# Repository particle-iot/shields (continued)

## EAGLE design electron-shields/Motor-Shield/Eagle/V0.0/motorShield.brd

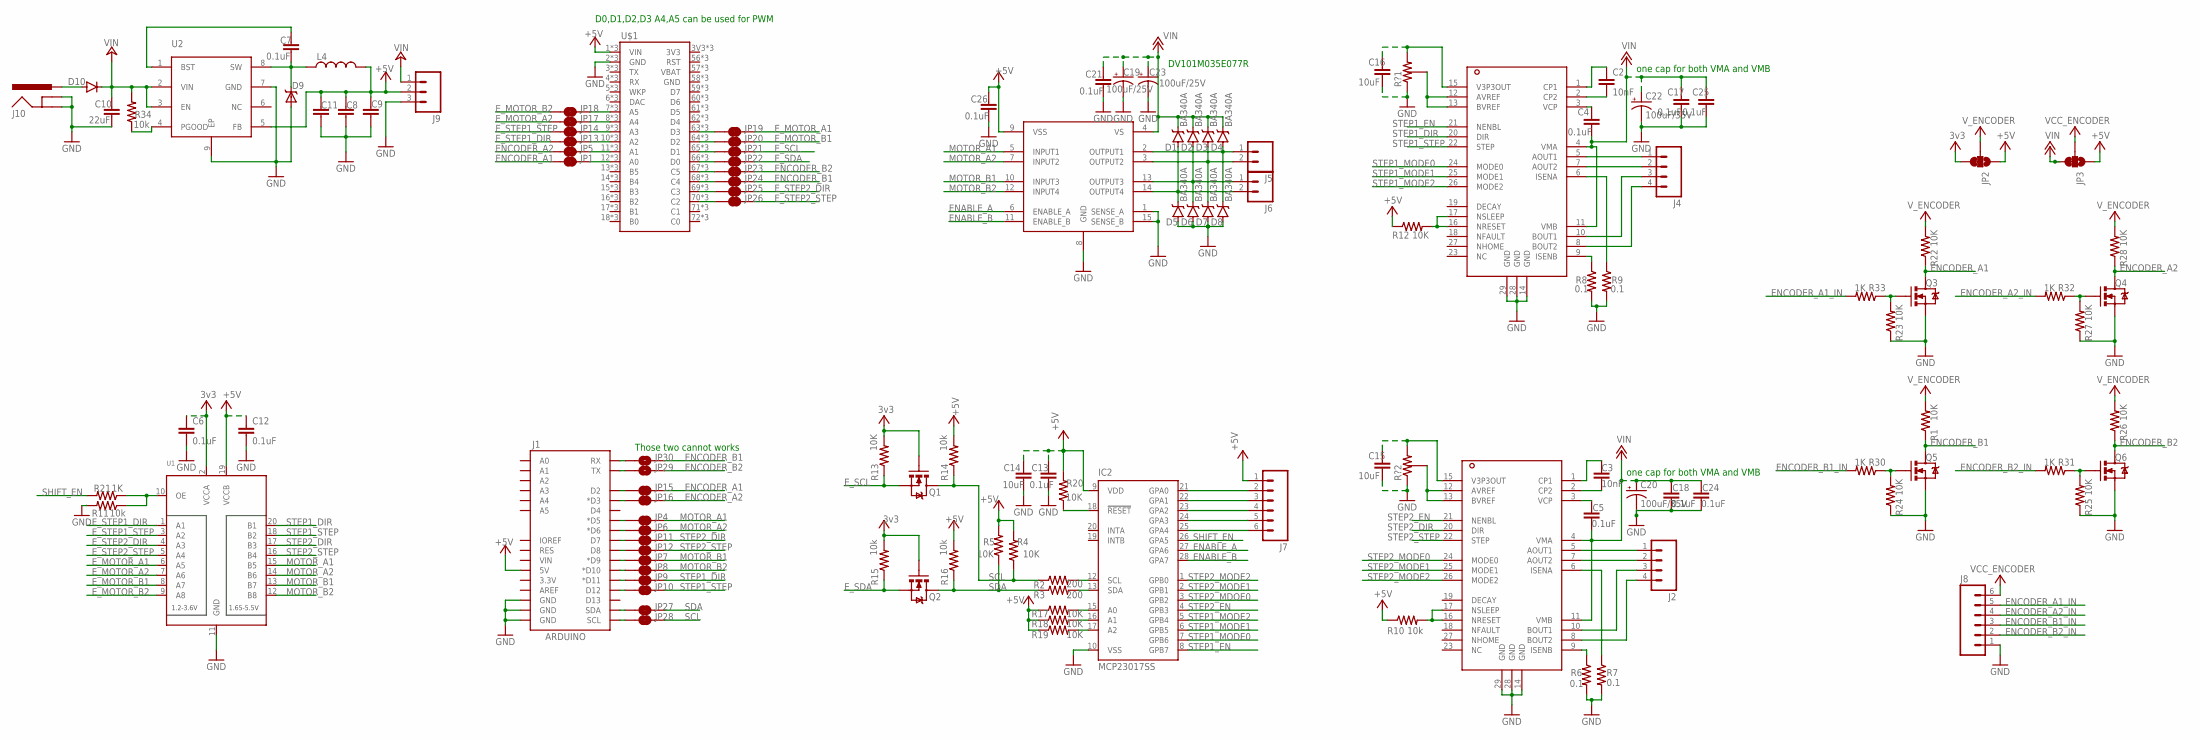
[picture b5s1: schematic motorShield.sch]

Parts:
C2, C3: 10nF; 0603
C4, C5, C6, C12, C13, C17, C18, C21, C24, C25, C26: 0.1uF; 0603
C7: 0.1uF; 0603-CAP
C8, C9, C11: 10UF10V10%(0805); 0805-CAP
C10: 22uF; 1210
C14, C15, C16: 10uF; 0603
C19, C23: 100uF/25V; PANASONIC_D
C20, C22: 100uF/35V; PANASONIC_D
D1, D2, D3, D4, D5, D6, D7, D8: BA340A; SMA-DIODE
D9: DIODE_SCHOTTKYA; DIODE_SMA
D10: DIODEB; DIODE-DO-220AA_NT(SMP)
IC2: MCP23017SS; SSOP28
J1: ARDUINO; UNO_R3_SHIELD_LOCK
J2, J4: M04SCREW; SCREWTERMINAL-3.5MM-4
J5, J6: M023.5MM_LOCK; SCREWTERMINAL-3.5MM-2_LOCK
J7, J8: M06POLAR; MOLEX-1X6
J9: M03SCREW; SCREWTERMINAL-3.5MM-3
J10: POWER_JACKPTH; POWER_JACK_PTH
JP1, JP4, JP5, JP6, JP7, JP8, JP9, JP10, JP11, JP12, JP13, JP14, JP15, JP16, JP17, JP18, JP19, JP20, JP21, JP22, JP23, JP24, JP25, JP26, JP27, JP28: JUMPER-PAD-2-NC_BY_TRACENO_SILK; PAD-JUMPER-2-NC_BY_TRACE_NO_SILK
JP2, JP3: JUMPER-PAD-3-2OF3_NC_BY_TRACE_LARGE; PAD-JUMPER-3-2OF3_NC_BY_TRACE_YES_SILK_LARGE
JP29, JP30: JUMPER-PAD-2-NO; PAD-JUMPER-2-NO_NO_SILK
L4: INDUCTOR4818; I4818
Q1, Q2, Q3, Q4, Q5, Q6: MOSFET-NCHANNELBSS138; SOT23
R1, R4, R5, R12, R13, R17, R18, R19, R20, R22, R23, R24, R25, R26, R27, R28: 10K; R0603
R2, R3: 200; R0603
R6, R7, R8, R9: 0.1; M1206
R10, R14, R15, R16: 10k; R0603
R11, R34: 10k; 0603-RES
R21: 1K; 0603-RES
R30, R31, R32, R33: 1K; R0603
R?1, R?2: POTENTIAL_RESISTOR
U1: TXB0108PWR; TSSOP20
U2: ADP2303; ADP2302
U$1: ELECTRONDUALROW; ELECTRON_DUAL-ROW
U?1, U?3: DRV8825
U?2: L298

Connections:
3V3: U$1.3V3, U$1.55 (3V3), U$1.91 (3V3)
+3V3: C6.1 (ANODE), JP2.3, Q1.1 (G), Q2.1 (G), R13.2, R15.2, U1.2 (VCCA)
+5V: C8.2, C9.2, C11.1, C12.1 (ANODE), C13.1 (ANODE), C14.1 (ANODE), C26.1 (ANODE), IC2.9 (VDD), J1.5V, J7.1, J8.6, J9.2, JP2.1, JP2.2, JP3.1, JP3.2, L4.2, R1.2, R4.2, R5.2, R10.1, R12.1, R14.2, R16.2, R17.1, R18.1, R19.1, R20.2, R22.2, R26.2, R28.2, U1.19 (VCCB), U2.5 (FB), U$1.1 (VIN), U$1.37 (VIN), U$1.VIN, U?2.9 (VSS)
+12V: C4.2 (CATHODE), C5.2 (CATHODE), C17.1 (ANODE), C18.1 (ANODE), C19.+, C20.+, C21.1 (ANODE), C22.+, C23.+, C24.1 (ANODE), C25.1 (ANODE), D1.C, D2.C, D3.C, D4.C, JP3.3, U?1.4 (VMA), U?1.11 (VMB), U?2.4 (VS), U?3.4 (VMA), U?3.11 (VMB)
+24V: C10.1, D10.CATHODE, J9.1, R34.2, U2.2 (VIN), U2.3 (EN)
ENABLE_A: IC2.27 (GPA6), U?2.6 (ENABLE_A)
ENABLE_B: IC2.28 (GPA7), U?2.11 (ENABLE_B)
ENCODER_A1: JP1.1, JP15.2, Q3.3 (D), R22.1
ENCODER_A1_IN: J8.5, R33.2
ENCODER_A2: JP5.1, JP16.2, Q4.3 (D), R28.1
ENCODER_A2_IN: J8.4, R32.2
ENCODER_B1: JP24.2, JP30.2, Q5.3 (D), R1.1
ENCODER_B1_IN: J8.3, R30.2
ENCODER_B2: JP23.2, JP29.2, Q6.3 (D), R26.1
ENCODER_B2_IN: J8.2, R31.2
E_MOTOR_A1: JP19.2, U1.6 (A5)
E_MOTOR_A2: JP17.1, U1.7 (A6)
E_MOTOR_B1: JP20.2, U1.8 (A7)
E_MOTOR_B2: JP18.1, U1.9 (A8)
E_SCL: JP21.2, Q1.2 (S), R13.1
E_SDA: JP22.2, Q2.2 (S), R15.1
E_STEP1_DIR: JP13.1, U1.1 (A1)
E_STEP1_STEP: JP14.1, U1.3 (A2)
E_STEP2_DIR: JP25.2, U1.4 (A3)
E_STEP2_STEP: JP26.2, U1.5 (A4)
GND: C6.2 (CATHODE), C8.1, C9.1, C10.2, C11.2, C12.2 (CATHODE), C13.2 (CATHODE), C14.2 (CATHODE), C15.2 (CATHODE), C16.2 (CATHODE), C17.2 (CATHODE), C18.2 (CATHODE), C19.-, C20.-, C21.2 (CATHODE), C22.-, C23.-, C24.2 (CATHODE), C25.2 (CATHODE), C26.2 (CATHODE), D5.A, D6.A, D7.A, D8.A, D9.ANODE, IC2.10 (VSS), J1.GND@0 (GND), J1.GND@1 (GND), J1.GND@2 (GND), J8.1, J9.3, J10.GND, J10.GNDBREAK, Q3.2 (S), Q4.2 (S), Q5.2 (S), Q6.2 (S), R6.2, R7.2, R8.2, R9.2, R11.2, R23.1, R24.1, R25.1, R27.1, R?1.1, R?2.1, U1.11 (GND), U2.7 (GND), U2.9 (EP), U$1.2 (GND), U$1.38 (GND), U$1.58 (GND), U$1.94 (GND), U$1.GND, U$1.GND@2 (GND), U?1.14 (GND), U?1.28 (GND), U?1.29 (GND), U?2.1 (SENSE_A), U?2.8 (GND), U?2.15 (SENSE_B), U?3.14 (GND), U?3.28 (GND), U?3.29 (GND)
MOTOR_A1: JP4.2, U1.15 (B5), U?2.5 (INPUT1)
MOTOR_A2: JP6.2, U1.14 (B6), U?2.7 (INPUT2)
MOTOR_B1: JP7.2, U1.13 (B7), U?2.10 (INPUT3)
MOTOR_B2: JP8.2, U1.12 (B8), U?2.12 (INPUT4)
unnamed: IC2.13 (SDA), R3.2
unnamed: IC2.12 (SCL), R2.2
unnamed: C3.2 (CATHODE), U?3.2 (CP2)
unnamed: C3.1 (ANODE), U?3.1 (CP1)
unnamed: C2.2 (CATHODE), U?1.2 (CP2)
unnamed: C2.1 (ANODE), U?1.1 (CP1)
unnamed: R6.1, U?3.9 (ISENB)
unnamed: R7.1, U?3.6 (ISENA)
unnamed: R10.2, U?3.16 (NRESET), U?3.17 (NSLEEP)
unnamed: D4.A, D8.C, J5.1, U?2.2 (OUTPUT1)
unnamed: J2.1, U?3.5 (AOUT1)
unnamed: J2.2, U?3.7 (AOUT2)
unnamed: J2.3, U?3.10 (BOUT1)
unnamed: J2.4, U?3.8 (BOUT2)
unnamed: R8.1, U?1.9 (ISENB)
unnamed: R9.1, U?1.6 (ISENA)
unnamed: J4.1, U?1.5 (AOUT1)
unnamed: J4.2, U?1.7 (AOUT2)
unnamed: J4.3, U?1.10 (BOUT1)
unnamed: J4.4, U?1.8 (BOUT2)
unnamed: C4.1 (ANODE), U?1.3 (VCP)
unnamed: C5.1 (ANODE), U?3.3 (VCP)
unnamed: D3.A, D7.C, J5.2, U?2.3 (OUTPUT2)
unnamed: D2.A, D6.C, J6.1, U?2.13 (OUTPUT3)
unnamed: D1.A, D5.C, J6.2, U?2.14 (OUTPUT4)
unnamed: R11.1, R21.1, U1.10 (OE)
unnamed: IC2.15 (A0), R17.2
unnamed: R12.2, U?1.16 (NRESET), U?1.17 (NSLEEP)
unnamed: IC2.16 (A1), R18.2
unnamed: IC2.17 (A2), R19.2
unnamed: R?1.3, U?1.12 (AVREF), U?1.13 (BVREF)
unnamed: IC2.18 (!RESET), R20.1
unnamed: J1.SCL, JP28.1
unnamed: R?2.3, U?3.12 (AVREF), U?3.13 (BVREF)
unnamed: J1.SDA, JP27.1
unnamed: J1.D5 (*D5), JP4.1
unnamed: J1.D6 (*D6), JP6.1
unnamed: J1.D9 (*D9), JP7.1
unnamed: J1.D10 (*D10), JP8.1
unnamed: J1.D11 (*D11), JP9.1
unnamed: J1.D12, JP10.1
unnamed: J1.D8, JP12.1
unnamed: J1.D7, JP11.1
unnamed: IC2.25 (GPA4), J7.6
unnamed: IC2.24 (GPA3), J7.5
unnamed: J1.D2, JP15.1
unnamed: J1.D3 (*D3), JP16.1
unnamed: IC2.23 (GPA2), J7.4
unnamed: IC2.22 (GPA1), J7.3
unnamed: IC2.21 (GPA0), J7.2
unnamed: Q4.1 (G), R27.2, R32.1
unnamed: Q5.1 (G), R24.2, R30.1
unnamed: Q6.1 (G), R25.2, R31.1
unnamed: C7.2, D9.CATHODE, L4.1, U2.8 (SW)
unnamed: Q3.1 (G), R23.2, R33.1
unnamed: C7.1, U2.1 (BST)
unnamed: R34.1, U2.4 (PGOOD)
unnamed: D10.ANODE, J10.PWR
unnamed: JP1.2, U$1.12 (A0), U$1.48 (A0), U$1.A0
unnamed: JP5.2, U$1.11 (A1), U$1.47 (A1), U$1.A1
unnamed: JP13.2, U$1.10 (A2), U$1.46 (A2), U$1.A2
unnamed: JP14.2, U$1.9 (A3), U$1.45 (A3), U$1.A3
unnamed: JP17.2, U$1.8 (A4), U$1.44 (A4), U$1.A4
unnamed: JP18.2, U$1.7 (A5), U$1.43 (A5), U$1.A5
unnamed: JP19.1, U$1.63 (D3), U$1.99 (D3), U$1.D3
unnamed: JP20.1, U$1.64 (D2), U$1.100 (D2), U$1.D2
unnamed: JP21.1, U$1.65 (D1), U$1.101 (D1), U$1.D1
unnamed: JP22.1, U$1.66 (D0), U$1.102 (D0), U$1.D0
unnamed: JP23.1, U$1.67 (C5), U$1.103 (C5), U$1.C5
unnamed: JP24.1, U$1.68 (C4), U$1.104 (C4), U$1.C4
unnamed: JP25.1, U$1.69 (C3), U$1.105 (C3), U$1.C3
unnamed: JP26.1, U$1.70 (C2), U$1.106 (C2), U$1.C2
unnamed: C15.1 (ANODE), R?2.2, U?3.15 (V3P3OUT)
unnamed: J1.TX, JP29.1
unnamed: J1.RX, JP30.1
unnamed: C16.1 (ANODE), R?1.2, U?1.15 (V3P3OUT)
SCL: JP28.2, Q1.3 (D), R2.1, R4.1, R14.1
SDA: JP27.2, Q2.3 (D), R3.1, R5.1, R16.1
SHIFT_EN: IC2.26 (GPA5), R21.2
STEP1_DIR: JP9.2, U1.20 (B1), U?1.20 (DIR)
STEP1_EN: IC2.8 (GPB7), U?1.21 (NENBL)
STEP1_MODE0: IC2.7 (GPB6), U?1.24 (MODE0)
STEP1_MODE1: IC2.6 (GPB5), U?1.25 (MODE1)
STEP1_MODE2: IC2.5 (GPB4), U?1.26 (MODE2)
STEP1_STEP: JP10.2, U1.18 (B2), U?1.22 (STEP)
STEP2_DIR: JP11.2, U1.17 (B3), U?3.20 (DIR)
STEP2_EN: IC2.4 (GPB3), U?3.21 (NENBL)
STEP2_MDOE0: IC2.3 (GPB2)
STEP2_MODE0: U?3.24 (MODE0)
STEP2_MODE1: IC2.2 (GPB1), U?3.25 (MODE1)
STEP2_MODE2: IC2.1 (GPB0), U?3.26 (MODE2)
STEP2_STEP: JP12.2, U1.16 (B4), U?3.22 (STEP)

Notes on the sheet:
D0,D1,D2,D3 A4,A5 can be used for PWM
DV101M035E077R
Those two cannot works
one cap for both VMA and VMB

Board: 2 copper layers, 123 parts (0 on the bottom side), 120 nets, no tracks yet.

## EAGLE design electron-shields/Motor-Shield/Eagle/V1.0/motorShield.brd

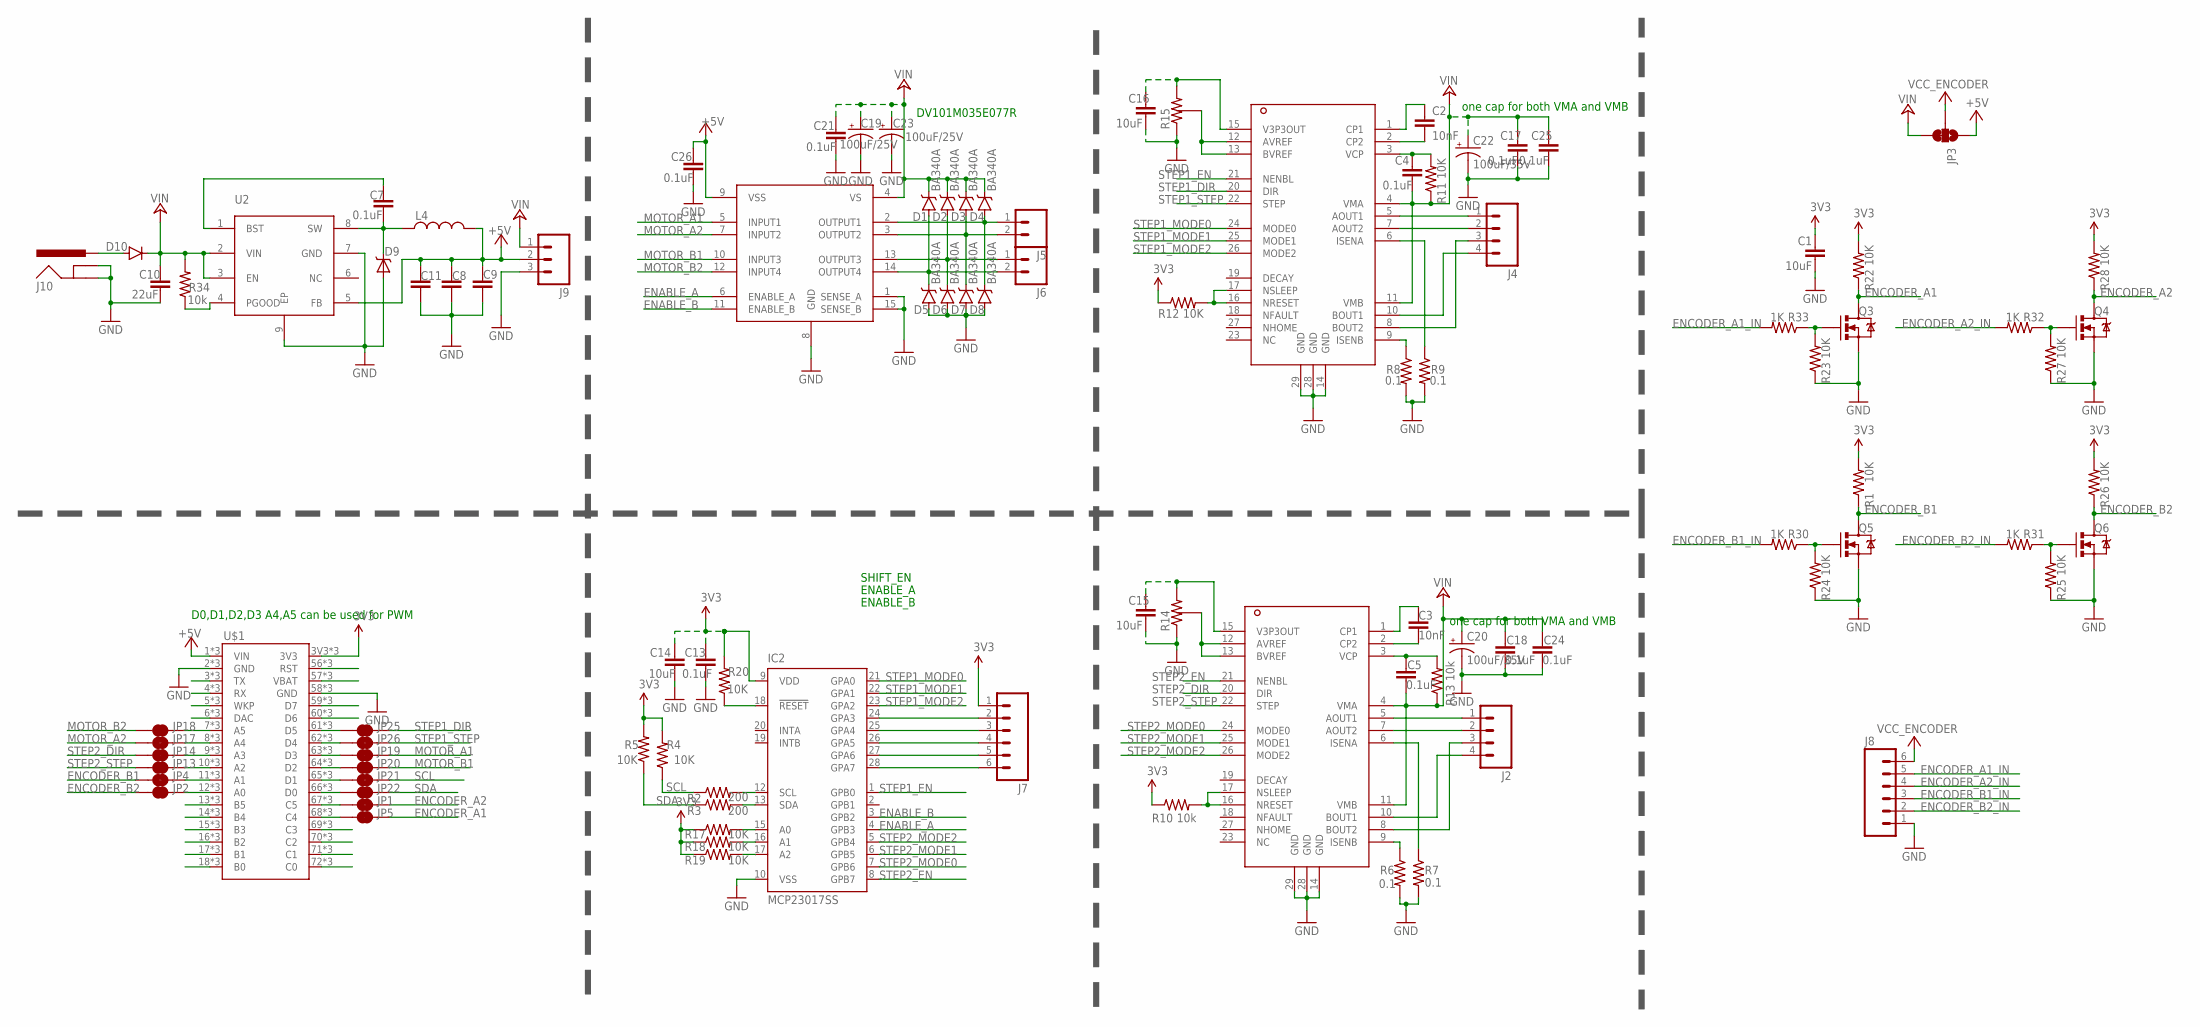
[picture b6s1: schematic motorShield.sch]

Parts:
C1, C14, C15, C16: 10uF; 0603
C2, C3: 10nF; 0603
C4, C5, C13, C17, C18, C21, C24, C25, C26: 0.1uF; 0603
C7: 0.1uF; 0603-CAP
C8, C9, C11: 10UF10V10%(0805); 0805-CAP
C10: 22uF; 1210
C19, C23: 100uF/25V; PANASONIC_D
C20, C22: 100uF/35V; PANASONIC_D
D1, D2, D3, D4, D5, D6, D7, D8: BA340A; SMA-DIODE
D9: DIODE_SCHOTTKYA; DIODE_SMA
D10: DIODEB; DIODE-DO-220AA_NT(SMP)
IC2: MCP23017SS; SSOP28
J2, J4: M04SCREW; SCREWTERMINAL-3.5MM-4
J5, J6: M023.5MM_LOCK; SCREWTERMINAL-3.5MM-2_LOCK
J7, J8: M06POLAR; MOLEX-1X6
J9: M03SCREW; SCREWTERMINAL-3.5MM-3
J10: POWER_JACKPTH; POWER_JACK_PTH
JP1, JP2, JP4, JP5, JP13, JP14, JP17, JP18, JP19, JP20, JP21, JP22, JP25, JP26: JUMPER-PAD-2-NC_BY_TRACENO_SILK; PAD-JUMPER-2-NC_BY_TRACE_NO_SILK
JP3: JUMPER-PAD-3-2OF3_NC_BY_TRACE_LARGE; PAD-JUMPER-3-2OF3_NC_BY_TRACE_YES_SILK_LARGE
L4: INDUCTOR4818; I4818
Q3, Q4, Q5, Q6: MOSFET-NCHANNELBSS138; SOT23
R1, R4, R5, R11, R12, R17, R18, R19, R20, R22, R23, R24, R25, R26, R27, R28: 10K; R0603
R2, R3: 200; R0603
R6, R7, R8, R9: 0.1; M1206
R10, R13: 10k; R0603
R14, R15: POTENTIAL_RESISTOR; POTENTIAL_RESISTOR_2
R30, R31, R32, R33: 1K; R0603
R34: 10k; 0603-RES
U2: ADP2303; ADP2302
U$1: ELECTRONDUALROW; ELECTRON_DUAL-ROW
U?1, U?3: DRV8825
U?2: L298

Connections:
+5V: C8.2, C9.2, C11.1, C26.1 (ANODE), J8.6, J9.2, JP3.1, JP3.2, L4.2, U2.5 (FB), U$1.1 (VIN), U$1.37 (VIN), U$1.VIN, U?2.9 (VSS)
+24V: C4.2 (CATHODE), C5.2 (CATHODE), C10.1, C17.1 (ANODE), C18.1 (ANODE), C19.+, C20.+, C21.1 (ANODE), C22.+, C23.+, C24.1 (ANODE), C25.1 (ANODE), D1.C, D2.C, D3.C, D4.C, D10.CATHODE, J9.1, JP3.3, R11.1, R13.1, R34.2, U2.2 (VIN), U2.3 (EN), U?1.4 (VMA), U?1.11 (VMB), U?2.4 (VS), U?3.4 (VMA), U?3.11 (VMB)
ENABLE_A: IC2.4 (GPB3), U?2.6 (ENABLE_A)
ENABLE_B: IC2.3 (GPB2), U?2.11 (ENABLE_B)
ENCODER_A1: JP5.2, Q3.3 (D), R22.1
ENCODER_A1_IN: J8.5, R33.2
ENCODER_A2: JP1.2, Q4.3 (D), R28.1
ENCODER_A2_IN: J8.4, R32.2
ENCODER_B1: JP4.1, Q5.3 (D), R1.1
ENCODER_B1_IN: J8.3, R30.2
ENCODER_B2: JP2.1, Q6.3 (D), R26.1
ENCODER_B2_IN: J8.2, R31.2
GND: C1.2 (CATHODE), C8.1, C9.1, C10.2, C11.2, C13.2 (CATHODE), C14.2 (CATHODE), C15.2 (CATHODE), C16.2 (CATHODE), C17.2 (CATHODE), C18.2 (CATHODE), C19.-, C20.-, C21.2 (CATHODE), C22.-, C23.-, C24.2 (CATHODE), C25.2 (CATHODE), C26.2 (CATHODE), D5.A, D6.A, D7.A, D8.A, D9.ANODE, IC2.10 (VSS), J8.1, J9.3, J10.GND, J10.GNDBREAK, Q3.2 (S), Q4.2 (S), Q5.2 (S), Q6.2 (S), R6.2, R7.2, R8.2, R9.2, R14.1, R15.1, R23.1, R24.1, R25.1, R27.1, U2.7 (GND), U2.9 (EP), U$1.2 (GND), U$1.38 (GND), U$1.58 (GND), U$1.94 (GND), U$1.GND, U$1.GND@2 (GND), U?1.14 (GND), U?1.28 (GND), U?1.29 (GND), U?2.1 (SENSE_A), U?2.8 (GND), U?2.15 (SENSE_B), U?3.14 (GND), U?3.28 (GND), U?3.29 (GND)
MOTOR_A1: JP19.2, U?2.5 (INPUT1)
MOTOR_A2: JP17.1, U?2.7 (INPUT2)
MOTOR_B1: JP20.2, U?2.10 (INPUT3)
MOTOR_B2: JP18.1, U?2.12 (INPUT4)
unnamed: IC2.13 (SDA), R3.2
unnamed: IC2.12 (SCL), R2.2
unnamed: C3.2 (CATHODE), U?3.2 (CP2)
unnamed: C3.1 (ANODE), U?3.1 (CP1)
unnamed: C2.2 (CATHODE), U?1.2 (CP2)
unnamed: C2.1 (ANODE), U?1.1 (CP1)
unnamed: R6.1, U?3.9 (ISENB)
unnamed: R7.1, U?3.6 (ISENA)
unnamed: R10.2, U?3.16 (NRESET), U?3.17 (NSLEEP)
unnamed: D4.A, D8.C, J5.1, U?2.2 (OUTPUT1)
unnamed: J2.1, U?3.5 (AOUT1)
unnamed: J2.2, U?3.7 (AOUT2)
unnamed: J2.4, U?3.10 (BOUT1)
unnamed: J2.3, U?3.8 (BOUT2)
unnamed: R8.1, U?1.9 (ISENB)
unnamed: R9.1, U?1.6 (ISENA)
unnamed: J4.1, U?1.5 (AOUT1)
unnamed: J4.2, U?1.7 (AOUT2)
unnamed: J4.4, U?1.10 (BOUT1)
unnamed: J4.3, U?1.8 (BOUT2)
unnamed: C4.1 (ANODE), R11.2, U?1.3 (VCP)
unnamed: C5.1 (ANODE), R13.2, U?3.3 (VCP)
unnamed: D3.A, D7.C, J5.2, U?2.3 (OUTPUT2)
unnamed: D2.A, D6.C, J6.1, U?2.13 (OUTPUT3)
unnamed: D1.A, D5.C, J6.2, U?2.14 (OUTPUT4)
unnamed: JP26.1, U$1.62 (D4), U$1.98 (D4), U$1.D4
unnamed: IC2.15 (A0), R17.2
unnamed: R12.2, U?1.16 (NRESET), U?1.17 (NSLEEP)
unnamed: IC2.16 (A1), R18.2
unnamed: IC2.17 (A2), R19.2
unnamed: R15.3, U?1.12 (AVREF), U?1.13 (BVREF)
unnamed: IC2.18 (!RESET), R20.1
unnamed: IC2.28 (GPA7), J7.6
unnamed: R14.3, U?3.12 (AVREF), U?3.13 (BVREF)
unnamed: IC2.27 (GPA6), J7.5
unnamed: IC2.26 (GPA5), J7.4
unnamed: IC2.25 (GPA4), J7.3
unnamed: IC2.24 (GPA3), J7.2
unnamed: JP25.1, U$1.61 (D5), U$1.97 (D5), U$1.D5
unnamed: JP1.1, U$1.67 (C5), U$1.103 (C5), U$1.C5
unnamed: JP2.2, U$1.12 (A0), U$1.48 (A0), U$1.A0
unnamed: JP4.2, U$1.11 (A1), U$1.47 (A1), U$1.A1
unnamed: JP5.1, U$1.68 (C4), U$1.104 (C4), U$1.C4
unnamed: U$1.72 (C0), U$1.108 (C0), U$1.C0
unnamed: U$1.71 (C1), U$1.107 (C1), U$1.C1
unnamed: U$1.70 (C2), U$1.106 (C2), U$1.C2
unnamed: U$1.69 (C3), U$1.105 (C3), U$1.C3
unnamed: U$1.60 (D6), U$1.96 (D6), U$1.D6
unnamed: Q4.1 (G), R27.2, R32.1
unnamed: Q5.1 (G), R24.2, R30.1
unnamed: Q6.1 (G), R25.2, R31.1
unnamed: C7.2, D9.CATHODE, L4.1, U2.8 (SW)
unnamed: Q3.1 (G), R23.2, R33.1
unnamed: C7.1, U2.1 (BST)
unnamed: R34.1, U2.4 (PGOOD)
unnamed: D10.ANODE, J10.PWR
unnamed: U$1.59 (D7), U$1.95 (D7), U$1.D7
unnamed: JP13.2, U$1.10 (A2), U$1.46 (A2), U$1.A2
unnamed: JP14.2, U$1.9 (A3), U$1.45 (A3), U$1.A3
unnamed: JP17.2, U$1.8 (A4), U$1.44 (A4), U$1.A4
unnamed: JP18.2, U$1.7 (A5), U$1.43 (A5), U$1.A5
unnamed: JP19.1, U$1.63 (D3), U$1.99 (D3), U$1.D3
unnamed: JP20.1, U$1.64 (D2), U$1.100 (D2), U$1.D2
unnamed: JP21.1, U$1.65 (D1), U$1.101 (D1), U$1.D1
unnamed: JP22.1, U$1.66 (D0), U$1.102 (D0), U$1.D0
unnamed: U$1.57 (VBAT), U$1.93 (VBAT), U$1.VBAT
unnamed: U$1.56 (RST), U$1.92 (RST), U$1.RST
unnamed: U$1.3 (TX), U$1.39 (TX), U$1.TX
unnamed: U$1.4 (RX), U$1.40 (RX), U$1.RX
unnamed: C15.1 (ANODE), R14.2, U?3.15 (V3P3OUT)
unnamed: U$1.5 (WKP), U$1.41 (WKP), U$1.WKP
unnamed: U$1.6 (DAC), U$1.42 (DAC), U$1.DAC
unnamed: U$1.13 (B5), U$1.49 (B5), U$1.B5
unnamed: U$1.14 (B4), U$1.50 (B4), U$1.B4
unnamed: C16.1 (ANODE), R15.2, U?1.15 (V3P3OUT)
unnamed: U$1.15 (B3), U$1.51 (B3), U$1.B3
unnamed: U$1.16 (B2), U$1.52 (B2), U$1.B2
unnamed: U$1.17 (B1), U$1.53 (B1), U$1.B1
unnamed: U$1.18 (B0), U$1.54 (B0), U$1.B0
SCL: JP21.2, R2.1, R4.1
SDA: JP22.2, R3.1, R5.1
STEP1_DIR: JP25.2, U?1.20 (DIR)
STEP1_EN: IC2.1 (GPB0), U?1.21 (NENBL)
STEP1_MODE0: IC2.21 (GPA0), U?1.24 (MODE0)
STEP1_MODE1: IC2.22 (GPA1), U?1.25 (MODE1)
STEP1_MODE2: IC2.23 (GPA2), U?1.26 (MODE2)
STEP1_STEP: JP26.2, U?1.22 (STEP)
STEP2_DIR: JP14.1, U?3.20 (DIR)
STEP2_EN: IC2.8 (GPB7), U?3.21 (NENBL)
STEP2_MODE0: IC2.7 (GPB6), U?3.24 (MODE0)
STEP2_MODE1: IC2.6 (GPB5), U?3.25 (MODE1)
STEP2_MODE2: IC2.5 (GPB4), U?3.26 (MODE2)
STEP2_STEP: JP13.1, U?3.22 (STEP)
VDD: C1.1 (ANODE), C13.1 (ANODE), C14.1 (ANODE), IC2.9 (VDD), J7.1, R1.2, R4.2, R5.2, R10.1, R12.1, R17.1, R18.1, R19.1, R20.2, R22.2, R26.2, R28.2, U$1.3V3, U$1.55 (3V3), U$1.91 (3V3)

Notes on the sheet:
D0,D1,D2,D3 A4,A5 can be used for PWM
DV101M035E077R
one cap for both VMA and VMB
SHIFT_EN
ENABLE_A
ENABLE_B

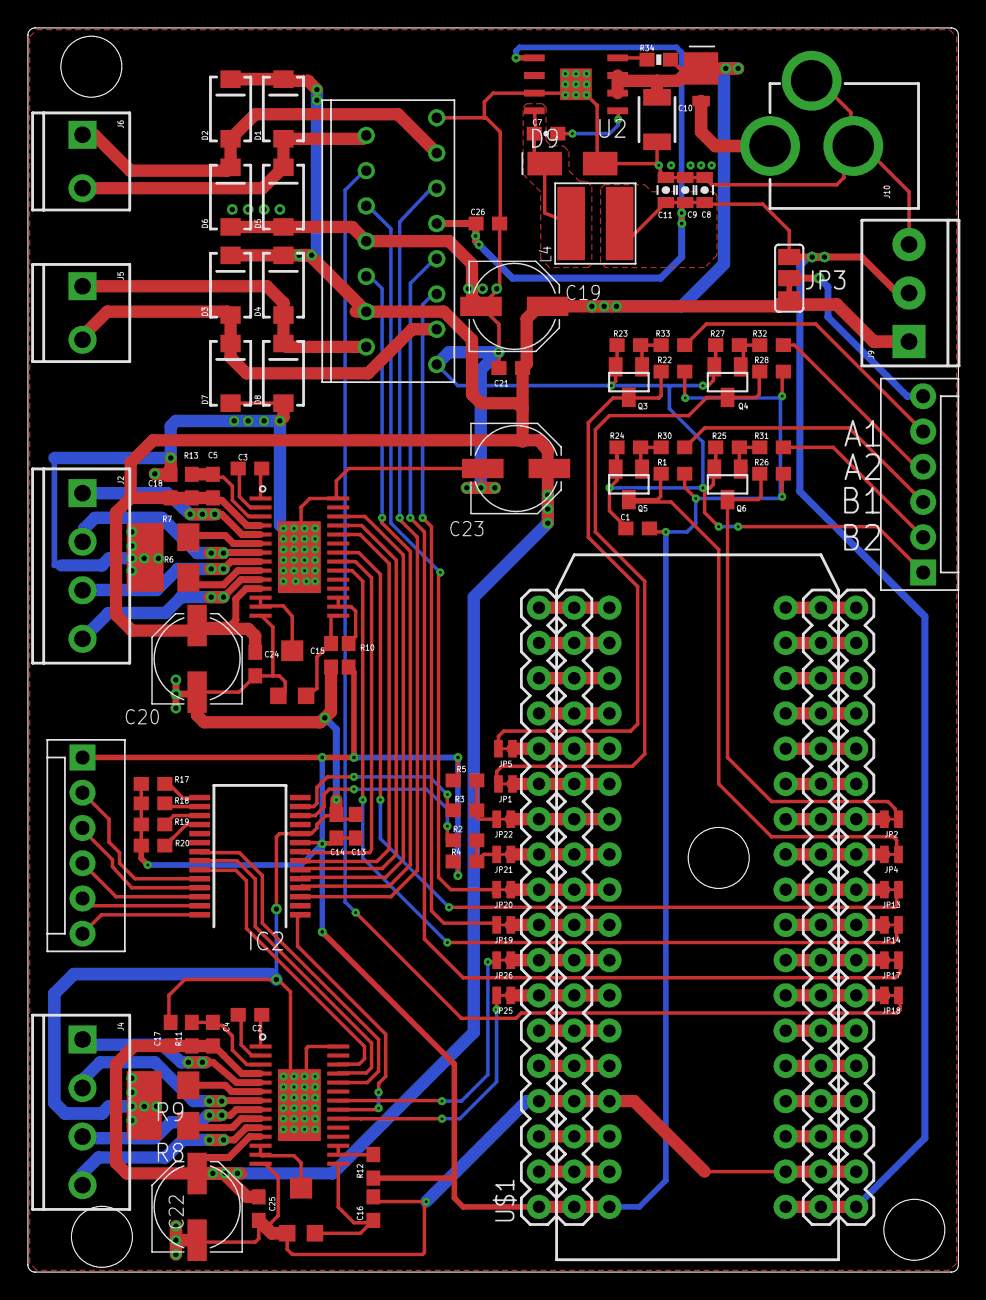
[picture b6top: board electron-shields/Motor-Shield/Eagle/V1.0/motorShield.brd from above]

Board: 2 copper layers, 67.1 x 89.7 mm, 99 parts (0 on the bottom side), 111 nets.

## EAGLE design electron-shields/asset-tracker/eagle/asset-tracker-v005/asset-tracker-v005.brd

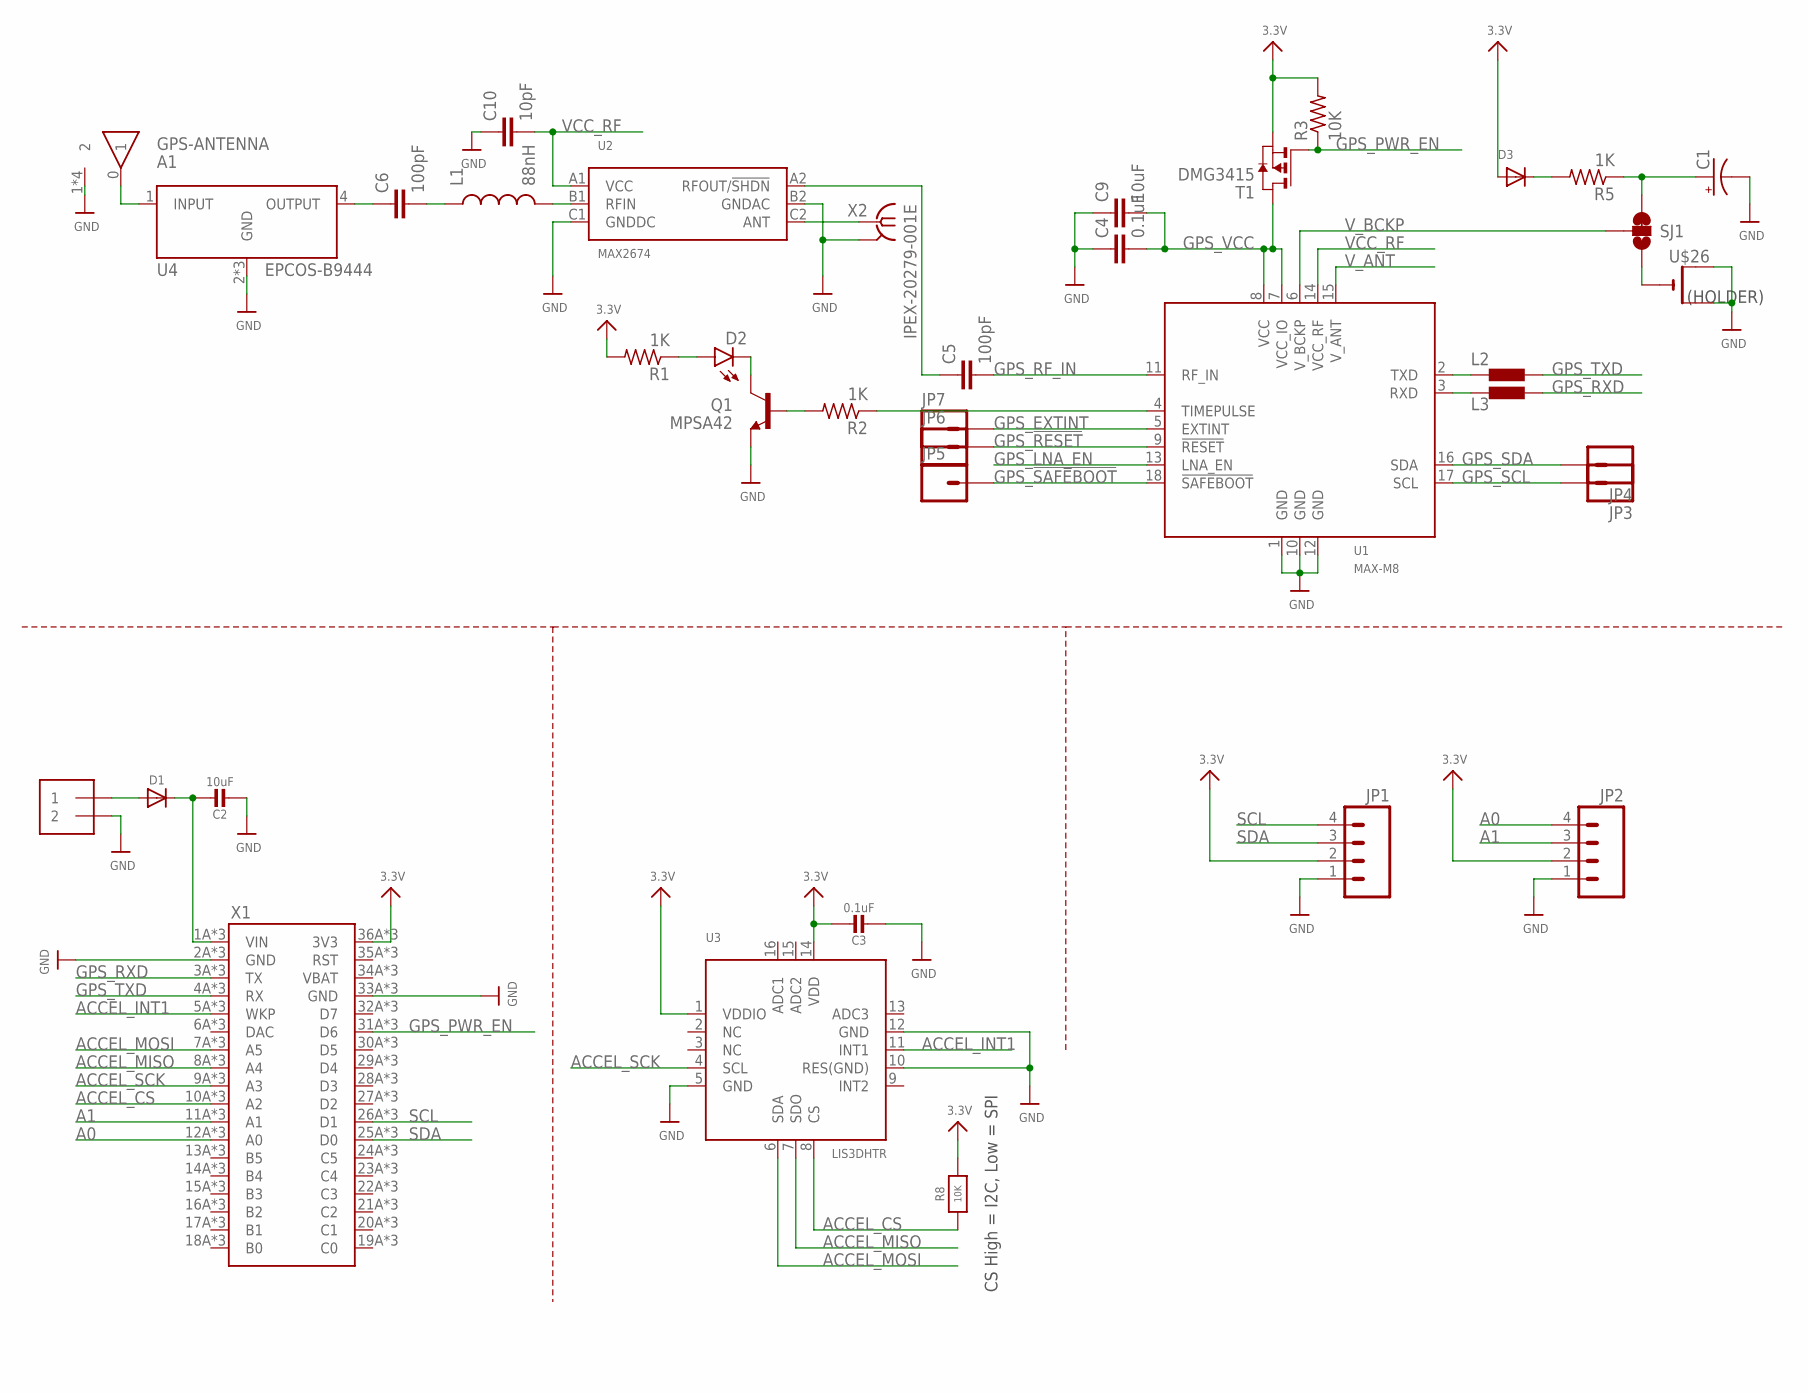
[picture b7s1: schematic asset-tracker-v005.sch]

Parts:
A1: GPS-ANTENNA; ANT1818B00BT1516S
C1: SUPERCAP; 414-VA5R
C2: 10uF; _0402MP
C3: 0.1uF; _0402MP
C4: 0.1uF; C0402
C5, C6: 100pF; C0402
C9: 10uF; C0402
C10: 10pF; C0402
D1: DIODESMA; SMADIODE
D2: LED0603; LED-0603
D3: DIODESOD-523; SOD-523
J1: 1X2-3.5MM
JP1, JP2: M04JST-PTH-VERT; JST-4-PTH-VERT
JP3, JP4, JP5, JP6, JP7: M01NOSILK-KIT; 1X01NS-KIT
L1: 88nH; C0402
L2, L3: BLM15HD102SN1; 0402
Q1: MPSA42; SOT23-3
R1, R2, R5: 1K; R0402
R3: 10K; R0402
R8: 10K; _0402MP
SJ1: JUMPER-PAD-3-2OF3_NC_BY_TRACE_LARGE; PAD-JUMPER-3-2OF3_NC_BY_TRACE_YES_SILK_LARGE
T1: DMG3415; SOT-23
U1: MAX-M8
U2: MAX2674; WLP-6
U3: LIS3DHTR; LGA16_3X3MM
U4: EPCOS-B9444; QCS5I
U$26: CR2032SMT; CR2032-SMD
X1: ELECTRON; ELECTRON_SMT
X2: IPEX-20279-001E

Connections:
3.3V: C3.1, D3.A, JP1.2, JP2.2, R1.2, R3.2, R8.2, T1.2 (S), U3.1 (VDDIO), U3.14 (VDD), X1.36A (3V3), X1.36B (3V3), X1.36C (3V3)
A0: JP2.4, X1.12A (A0), X1.12B (A0), X1.12C (A0)
A1: JP2.3, X1.11A (A1), X1.11B (A1), X1.11C (A1)
ACCEL_CS: R8.1, U3.8 (CS), X1.10A (A2), X1.10B (A2), X1.10C (A2)
ACCEL_INT1: U3.11 (INT1), X1.5A (WKP), X1.5B (WKP), X1.5C (WKP)
ACCEL_MISO: U3.7 (SDO), X1.8A (A4), X1.8B (A4), X1.8C (A4)
ACCEL_MOSI: U3.6 (SDA), X1.7A (A5), X1.7B (A5), X1.7C (A5)
ACCEL_SCK: U3.4 (SCL), X1.9A (A3), X1.9B (A3), X1.9C (A3)
GND: A1.1 (2), A1.2, A1.3 (2), A1.4 (2), C1.-, C2.2, C3.2, C4.1, C9.1, C10.1, J1.2, JP1.1, JP2.1, Q1.2 (E), U1.1 (GND), U1.10 (GND), U1.12 (GND), U2.B2 (GNDAC), U2.C1 (GNDDC), U3.5 (GND), U3.10 (RES(GND)), U3.12 (GND), U4.2 (GND), U4.3 (GND), U4.5 (GND), U$26.+$1 (+), U$26.+$2 (+1), X1.2A (GND), X1.2B (GND), X1.2C (GND), X1.33A (GND), X1.33B (GND), X1.33C (GND), X2.2@1 (GND), X2.2@2 (GND)
GPS_!RESET: JP6.1, U1.9 (!RESET)
GPS_!SAFEBOOT: JP5.1, U1.18 (!SAFEBOOT)
GPS_EXTINT: JP7.1, U1.5 (EXTINT)
GPS_LNA_EN: U1.13 (LNA_EN)
GPS_PWR_EN: R3.1, T1.3 (G), X1.31A (D6), X1.31B (D6), X1.31C (D6)
GPS_RF_IN: C5.2, U1.11 (RF_IN)
GPS_RXD: L3.2, X1.3A (TX), X1.3B (TX), X1.3C (TX)
GPS_SCL: JP3.1, U1.17 (SCL)
GPS_SDA: JP4.1, U1.16 (SDA)
GPS_TXD: L2.2, X1.4A (RX), X1.4B (RX), X1.4C (RX)
GPS_VCC: C4.2, C9.2, T1.1 (D), U1.7 (VCC_IO), U1.8 (VCC)
unnamed: C6.1, U4.4 (OUTPUT)
unnamed: L1.2, U2.B1 (RFIN)
unnamed: C6.2, L1.1
unnamed: C5.1, U2.A2 (RFOUT/!SHDN)
unnamed: U2.C2 (ANT), X2.1
unnamed: R2.1, U1.4 (TIMEPULSE)
unnamed: C1.+, R5.1, SJ1.3
unnamed: C2.1, D1.C, X1.1A (VIN), X1.1B (VIN), X1.1C (VIN)
unnamed: D1.A, J1.1
unnamed: D3.K (C), R5.2
unnamed: SJ1.1, U$26.-
unnamed: A1.0 (1), U4.1 (INPUT)
unnamed: Q1.1 (B), R2.2
unnamed: D2.C, Q1.3 (C)
unnamed: D2.A, R1.1
unnamed: L2.1, U1.2 (TXD)
unnamed: L3.1, U1.3 (RXD)
SCL: JP1.4, X1.26A (D1), X1.26B (D1), X1.26C (D1)
SDA: JP1.3, X1.25A (D0), X1.25B (D0), X1.25C (D0)
VCC_RF: C10.2, U1.14 (VCC_RF), U2.A1 (VCC)
V_ANT: U1.15 (V_ANT)
V_BCKP: SJ1.2, U1.6 (V_BCKP)

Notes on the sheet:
CS High = I2C, Low = SPI
(HOLDER)

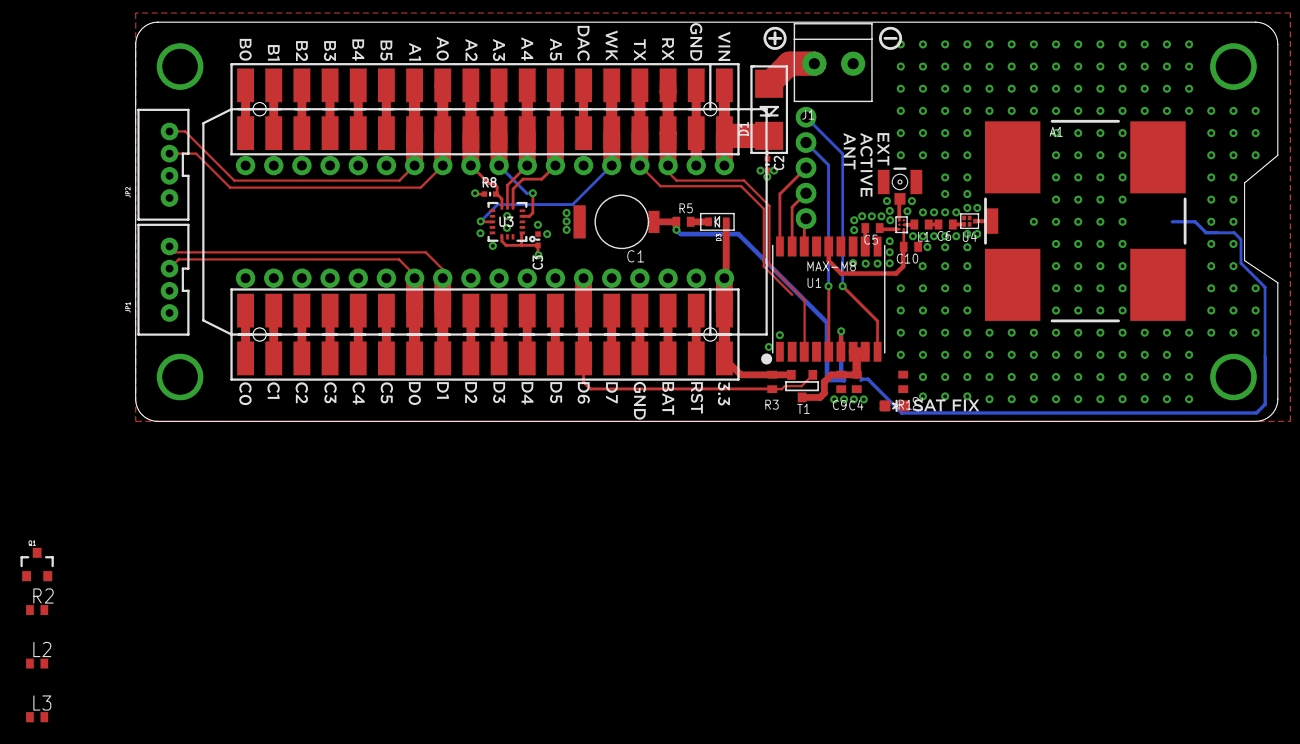
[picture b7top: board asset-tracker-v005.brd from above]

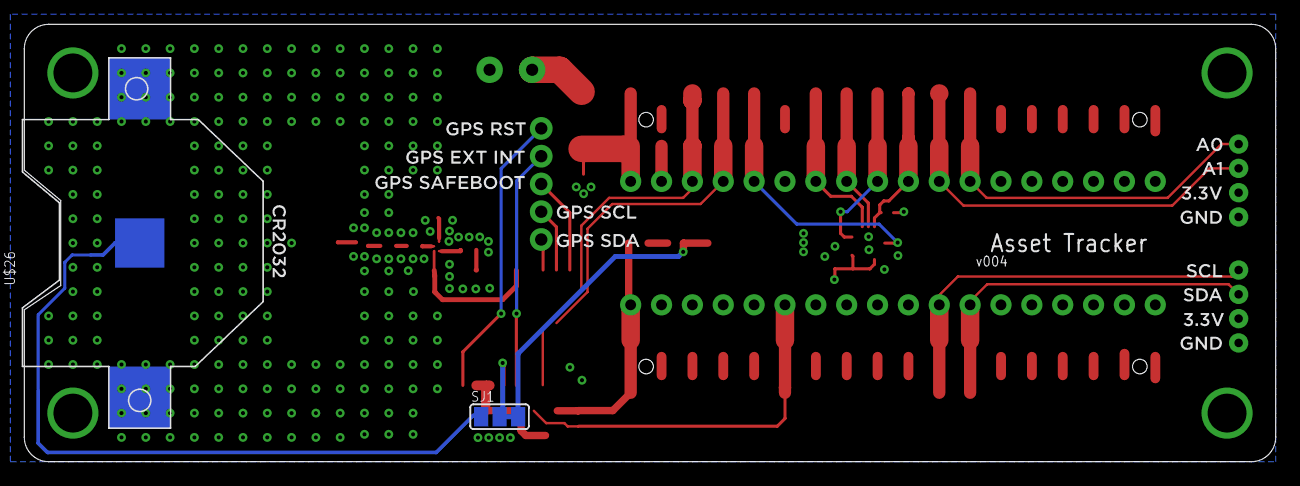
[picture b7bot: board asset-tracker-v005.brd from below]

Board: 4 copper layers, 103.0 x 36.0 mm, 38 parts (2 on the bottom side), 40 nets.

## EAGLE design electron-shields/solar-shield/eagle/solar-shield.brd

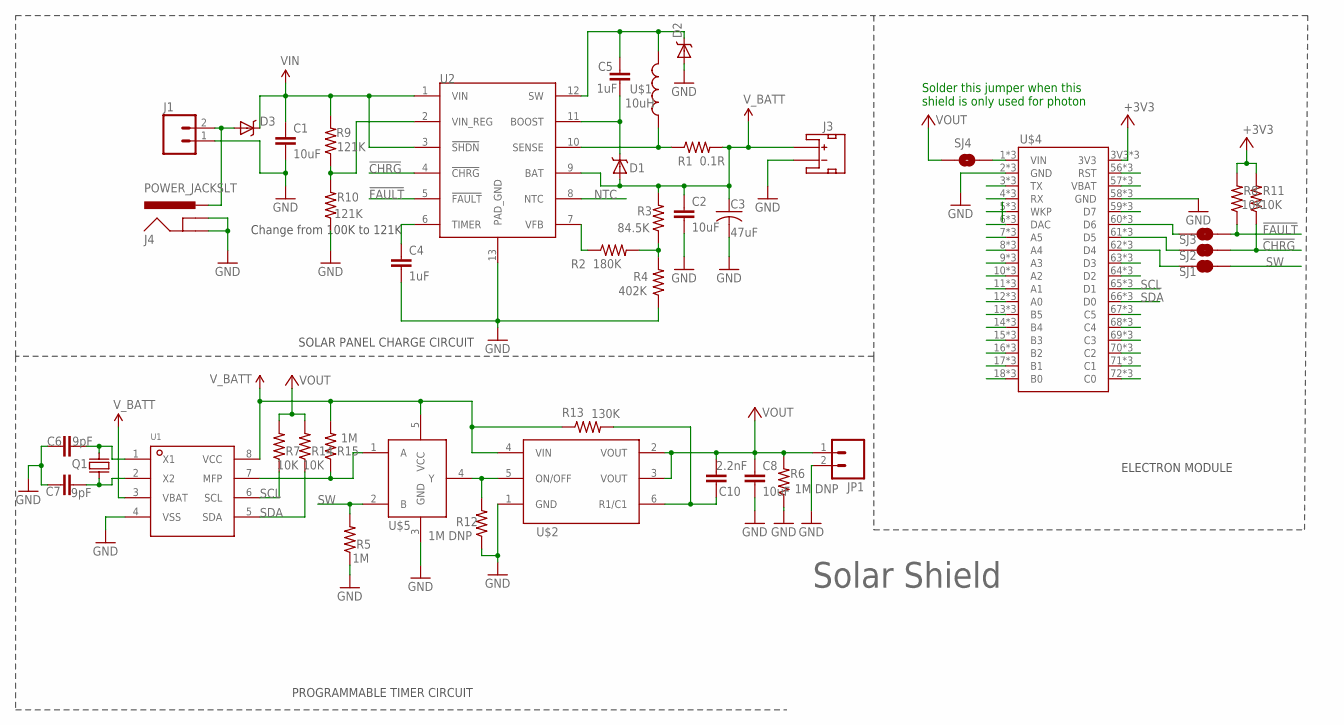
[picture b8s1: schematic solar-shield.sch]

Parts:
C1, C2: 10uF; 1206
C3: 47uF; 47U_TAN
C4, C5: 1uF; 0603
C6, C7: 9pF; 0603
C8: 10uF; 0805
C10: 2.2nF; 0603
D1: DIODE_SCHOTTKYD; DIODE_SOD323
D2, D3: DIODE_SCHOTTKYA; DIODE_SMA
J1: M025MM; SCREWTERMINAL-5MM-2
J3: JST_2MM_MALEA; JST_2_MSD_VERT
J4: POWER_JACKSLT; POWER_JACK_SLOT
JP1: M02PTH; 1X02
Q1: Q_FC135; FC135
R1: 0.1R; R0805
R2: 180K; 0603
R3: 84.5K; 0603
R4: 402K; 0603
R5, R15: 1M; 0603
R6, R12: 1M DNP; 0603
R7, R8, R11, R14: 10K; 0603
R9, R10: 121K; 0603
R13: 130K; 0603
SJ1, SJ2, SJ3: JUMPER-PAD-2-NC_BY_TRACE; PAD-JUMPER-2-NC_BY_TRACE_YES_SILK
SJ4: JUMPER-PAD-2-NO; PAD-JUMPER-2-NO_NO_SILK
U1: RTC_MCP7941X
U2: LT3652A; DFN_3X3
U$1: 10uH; INDUCTOR_NR6045T100M
U$2: TPS27082L
U$4: ELECTRONDUALROW; ELECTRON_DUAL-ROW
U$5: SN74UP1G32A; SN74UP1G32_DBV

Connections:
!CHRG: R11.1, SJ2.2, U2.4 (!CHRG)
!FAULT: R8.1, SJ3.2, U2.5 (!FAULT)
+3V3: R8.2, R11.2, U$4.3V3, U$4.55 (3V3), U$4.91 (3V3)
GND: C1.2 (CATHODE), C2.2 (CATHODE), C3.C (2), C4.2 (CATHODE), C6.1 (ANODE), C7.1 (ANODE), C8.2 (CATHODE), D2.ANODE, J1.1, J3.GND (-), J4.GND@1 (GNDBREAK), J4.GND@2 (GND), JP1.2, R4.1, R5.1, R6.1, R10.1, R12.1, U1.4 (VSS), U2.13 (PAD_GND), U$2.1 (GND), U$4.2 (GND), U$4.38 (GND), U$4.58 (GND), U$4.94 (GND), U$4.GND, U$4.GND@2 (GND), U$5.3 (GND)
unnamed: R2.2, R3.1, R4.2
unnamed: C5.2 (CATHODE), D1.CATHODE, U2.11 (BOOST)
unnamed: R1.1, U2.10 (SENSE), U$1.P$1 (1)
unnamed: R2.1, U2.7 (VFB)
unnamed: D3.ANODE, J1.2, J4.PWR
unnamed: C5.1 (ANODE), D2.CATHODE, U2.12 (SW), U$1.P$2 (2)
unnamed: U$4.3 (TX), U$4.39 (TX), U$4.TX
unnamed: U$4.4 (RX), U$4.40 (RX), U$4.RX
unnamed: U$4.5 (WKP), U$4.41 (WKP), U$4.WKP
unnamed: U$4.6 (DAC), U$4.42 (DAC), U$4.DAC
unnamed: U$4.7 (A5), U$4.43 (A5), U$4.A5
unnamed: U$4.8 (A4), U$4.44 (A4), U$4.A4
unnamed: U$4.9 (A3), U$4.45 (A3), U$4.A3
unnamed: U$4.10 (A2), U$4.46 (A2), U$4.A2
unnamed: U$4.11 (A1), U$4.47 (A1), U$4.A1
unnamed: U$4.12 (A0), U$4.48 (A0), U$4.A0
unnamed: U$4.13 (B5), U$4.49 (B5), U$4.B5
unnamed: U$4.14 (B4), U$4.50 (B4), U$4.B4
unnamed: U$4.15 (B3), U$4.51 (B3), U$4.B3
unnamed: U$4.16 (B2), U$4.52 (B2), U$4.B2
unnamed: U$4.17 (B1), U$4.53 (B1), U$4.B1
unnamed: U$4.18 (B0), U$4.54 (B0), U$4.B0
unnamed: U$4.72 (C0), U$4.108 (C0), U$4.C0
unnamed: U$4.71 (C1), U$4.107 (C1), U$4.C1
unnamed: U$4.70 (C2), U$4.106 (C2), U$4.C2
unnamed: U$4.69 (C3), U$4.105 (C3), U$4.C3
unnamed: U$4.68 (C4), U$4.104 (C4), U$4.C4
unnamed: U$4.67 (C5), U$4.103 (C5), U$4.C5
unnamed: SJ4.2, U$4.1 (VIN), U$4.37 (VIN), U$4.VIN
unnamed: U$4.64 (D2), U$4.100 (D2), U$4.D2
unnamed: U$4.59 (D7), U$4.95 (D7), U$4.D7
unnamed: U$4.57 (VBAT), U$4.93 (VBAT), U$4.VBAT
unnamed: U$4.56 (RST), U$4.92 (RST), U$4.RST
unnamed: SJ1.1, U$4.62 (D4), U$4.98 (D4), U$4.D4
unnamed: SJ2.1, U$4.61 (D5), U$4.97 (D5), U$4.D5
unnamed: SJ3.1, U$4.60 (D6), U$4.96 (D6), U$4.D6
unnamed: C6.2 (CATHODE), Q1.X2 (2), U1.1 (X1)
unnamed: C10.1 (ANODE), R13.2, U$2.6 (R1/C1)
unnamed: C7.2 (CATHODE), Q1.X1 (1), U1.2 (X2)
unnamed: R15.1, U1.7 (MFP), U$5.1 (A)
unnamed: R12.2, U$2.5 (ON/OFF), U$5.4 (Y)
NTC: U2.8 (NTC)
SCL: R7.1, U1.6 (SCL), U$4.65 (D1), U$4.101 (D1), U$4.D1
SDA: R14.1, U1.5 (SDA), U$4.66 (D0), U$4.102 (D0), U$4.D0
SET: R9.1, R10.2, U2.2 (VIN_REG)
SW: R5.2, SJ1.2, U$5.2 (B)
TCAL: U$4.63 (D3), U$4.99 (D3), U$4.D3
TIMER: C4.1 (ANODE), U2.6 (TIMER)
VCC: C8.1 (ANODE), C10.2 (CATHODE), JP1.1, R6.2, R7.2, R14.2, SJ4.1, U$2.2 (VOUT), U$2.3 (VOUT)
VIN: C1.1 (ANODE), D3.CATHODE, R9.2, U2.1 (VIN), U2.3 (!SHDN!)
V_BATT: C2.1 (ANODE), C3.A (1), D1.ANODE, J3.VCC (+), R1.2, R3.2, R13.1, R15.2, U1.3 (VBAT), U1.8 (VCC), U2.9 (BAT), U$2.4 (VIN), U$5.5 (VCC)

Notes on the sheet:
Solar Shield
ELECTRON MODULE
SOLAR PANEL CHARGE CIRCUIT
PROGRAMMABLE TIMER CIRCUIT
Solder this jumper when this shield is only used for photon
Change from 100K to 121K
